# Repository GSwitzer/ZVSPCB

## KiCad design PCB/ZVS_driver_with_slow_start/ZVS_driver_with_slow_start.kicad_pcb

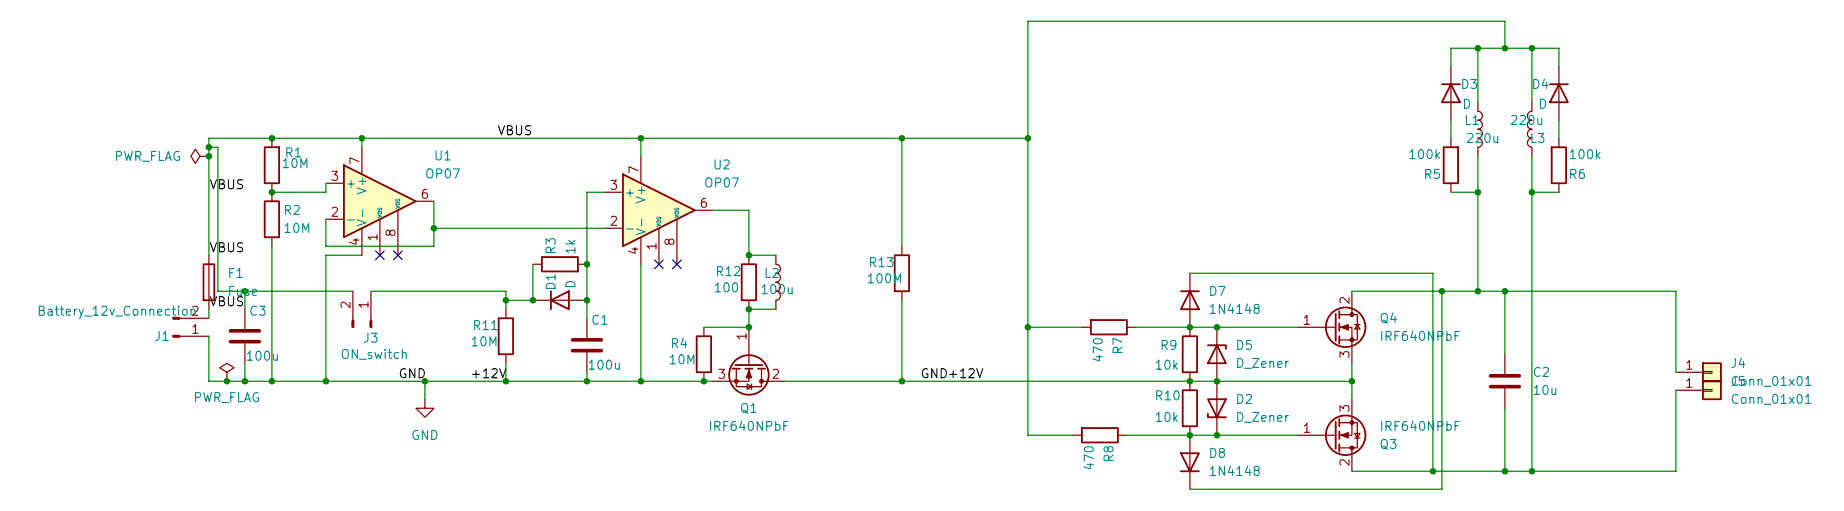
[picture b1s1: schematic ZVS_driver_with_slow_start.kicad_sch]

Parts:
C1, C3: 100u; C_0805_2012Metric
C2: 10u; C_Rect_L16.5mm_W9.0mm_P15.00mm_MKT
D1: D; D_0805_2012Metric_Pad1.15x1.40mm_HandSolder
D2, D5: D_Zener; D_A-405_P7.62mm_Horizontal
D3, D4: D; D_A-405_P10.16mm_Horizontal
D7, D8: 1N4148; D_DO-35_SOD27_P7.62mm_Horizontal
F1: Fuse; Fuseholder_Clip-5x20mm_Keystone_3517_Inline_P23.11x6.76mm_D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
J1: Battery_12v_Connection; AMASS_XT30U-F_1x02_P5.0mm_Vertical
J3: ON_switch; AMASS_XT30U-F_1x02_P5.0mm_Vertical
J4, J5: Conn_01x01; TerminalBlock_MetzConnect_360271_1x01_Horizontal_ScrewM3.0_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
L1, L3: 220u; L_Toroid_Vertical_L14.0mm_W6.3mm_P4.57mm_Pulse_A
L2: 100u; L_Coilcraft_LPS4414
Q1, Q3, Q4: IRF640NPbF; TO-220-3_Vertical
R1, R2, R4, R11: 10M; R_0805_2012Metric
R3: 1k; R_0805_2012Metric_Pad1.20x1.40mm_HandSolder
R5, R6: 100k; R_Axial_DIN0207_L6.3mm_D2.5mm_P7.62mm_Horizontal
R7, R8: 470; R_Axial_DIN0207_L6.3mm_D2.5mm_P7.62mm_Horizontal
R9, R10: 10k; R_Axial_DIN0207_L6.3mm_D2.5mm_P7.62mm_Horizontal
R12: 100; R_0805_2012Metric
R13: 100M; R_Axial_DIN0207_L6.3mm_D2.5mm_P7.62mm_Horizontal
U1, U2: OP07; SOIC-8_3.9x4.9mm_P1.27mm

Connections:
/VBUS: C3.1, D3.1 (K), D4.1 (K), F1.1, F1.2, J1.2, J3.2, L1.1, L3.2, R1.2, R7.2, R8.2, R13.1, U1.7 (V+), U2.7 (V+)
GND: C1.2, C3.2, D2.2 (A), D5.2 (A), J1.1, Q1.2 (D), Q1.3 (S), Q3.3 (S), Q4.3 (S), R2.2, R4.2, R9.2, R10.1, R11.2, R13.2, U1.4 (V-), U2.4 (V-)
unnamed: C1.1, D1.2 (A), R3.2, U2.3 (+)
unnamed: D1.1 (K), J3.1, R3.1, R11.1
unnamed: D2.1 (K), D8.2 (A), Q3.1 (G), R8.1, R10.2
unnamed: D3.2 (A), R5.2
unnamed: D4.2 (A), R6.2
unnamed: D5.1 (K), D7.2 (A), Q4.1 (G), R7.1, R9.1
unnamed: C2.2, D7.1 (K), J5.1, L3.1, Q3.2 (D), R6.1
unnamed: C2.1, D8.1 (K), J4.1, L1.2, Q4.2 (D), R5.1
unnamed: L2.1, R12.1, U2.6
unnamed: L2.2, Q1.1 (G), R4.1, R12.2
unnamed: R1.1, R2.1, U1.3 (+)
unnamed: U1.2 (-), U1.6, U2.2 (-)

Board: 2 copper layers, 36 parts (0 on the bottom side), 14 nets, no tracks yet.

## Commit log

2025-04-25 added curent limiting RL on Q1
2025-04-25 added fuse and cleaned up board
2025-04-25 added sim
2025-04-30 the PCB is taking some serious shape
2025-04-30 removed superflous power switch
